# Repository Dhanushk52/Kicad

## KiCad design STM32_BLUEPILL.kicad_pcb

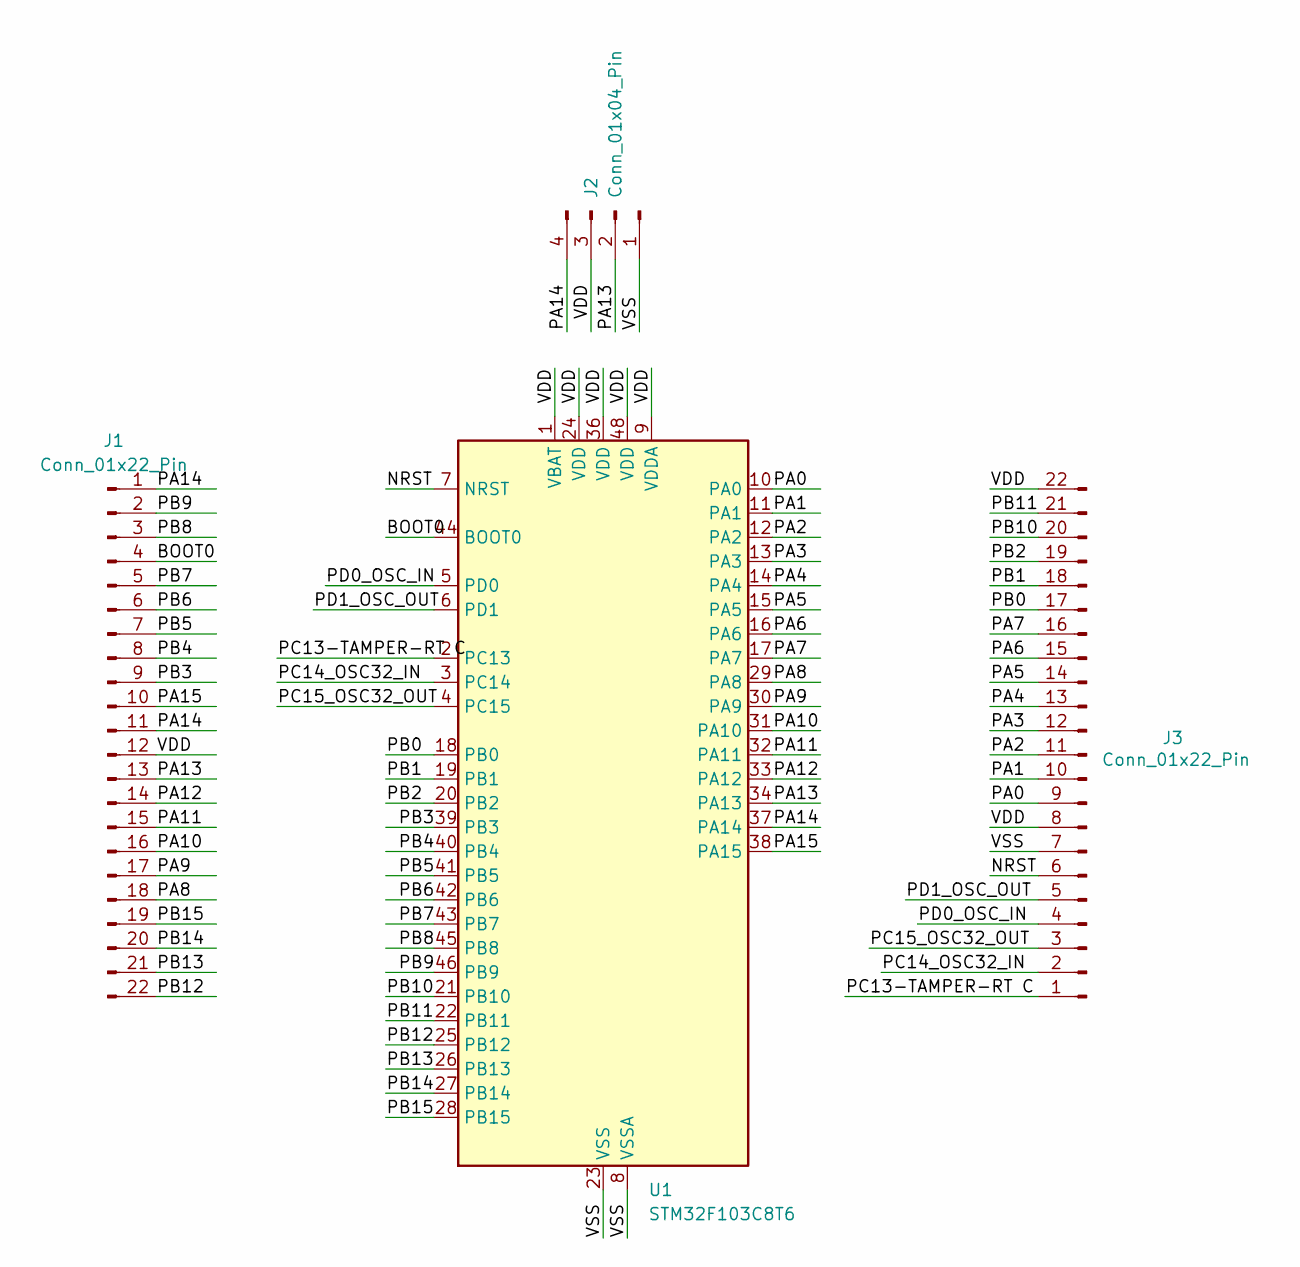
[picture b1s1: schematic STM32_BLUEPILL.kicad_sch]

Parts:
J1, J3: Conn_01x22_Pin; PinHeader_1x22_P2.54mm_Vertical
J2: Conn_01x04_Pin; PinHeader_1x04_P2.54mm_Horizontal
U1: STM32F103C8T6; LQFP-48_7x7mm_P0.5mm

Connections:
/BOOT0: J1.4, U1.44 (BOOT0)
/NRST: J3.6, U1.7 (NRST)
/PA0: J3.9, U1.10 (PA0)
/PA1: J3.10, U1.11 (PA1)
/PA2: J3.11, U1.12 (PA2)
/PA3: J3.12, U1.13 (PA3)
/PA4: J3.13, U1.14 (PA4)
/PA5: J3.14, U1.15 (PA5)
/PA6: J3.15, U1.16 (PA6)
/PA7: J3.16, U1.17 (PA7)
/PA8: J1.18, U1.29 (PA8)
/PA9: J1.17, U1.30 (PA9)
/PA10: J1.16, U1.31 (PA10)
/PA11: J1.15, U1.32 (PA11)
/PA12: J1.14, U1.33 (PA12)
/PA13: J1.13, J2.2, U1.34 (PA13)
/PA14: J1.1, J1.11, J2.4, U1.37 (PA14)
/PA15: J1.10, U1.38 (PA15)
/PB0: J3.17, U1.18 (PB0)
/PB1: J3.18, U1.19 (PB1)
/PB2: J3.19, U1.20 (PB2)
/PB3: J1.9, U1.39 (PB3)
/PB4: J1.8, U1.40 (PB4)
/PB5: J1.7, U1.41 (PB5)
/PB6: J1.6, U1.42 (PB6)
/PB7: J1.5, U1.43 (PB7)
/PB8: J1.3, U1.45 (PB8)
/PB9: J1.2, U1.46 (PB9)
/PB10: J3.20, U1.21 (PB10)
/PB11: J3.21, U1.22 (PB11)
/PB12: J1.22, U1.25 (PB12)
/PB13: J1.21, U1.26 (PB13)
/PB14: J1.20, U1.27 (PB14)
/PB15: J1.19, U1.28 (PB15)
/PC13-TAMPER-RT C: J3.1, U1.2 (PC13)
/PC14_OSC32_IN: J3.2, U1.3 (PC14)
/PC15_OSC32_OUT: J3.3, U1.4 (PC15)
/PD0_OSC_IN: J3.4, U1.5 (PD0)
/PD1_OSC_OUT: J3.5, U1.6 (PD1)
/VDD: J1.12, J2.3, J3.8, J3.22, U1.1 (VBAT), U1.9 (VDDA), U1.24 (VDD), U1.36 (VDD), U1.48 (VDD)
/VSS: J2.1, J3.7, U1.8 (VSSA), U1.23 (VSS), U1.35 (VSS), U1.47 (VSS)

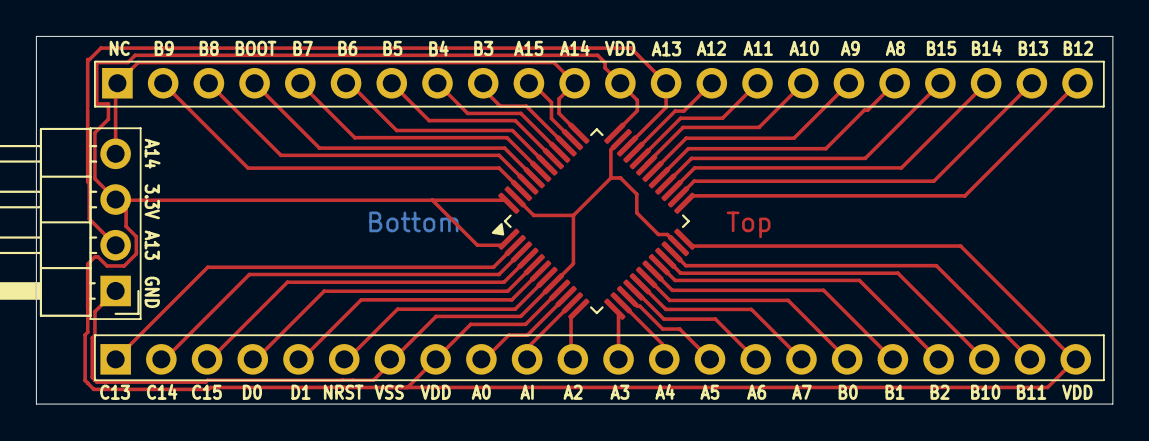
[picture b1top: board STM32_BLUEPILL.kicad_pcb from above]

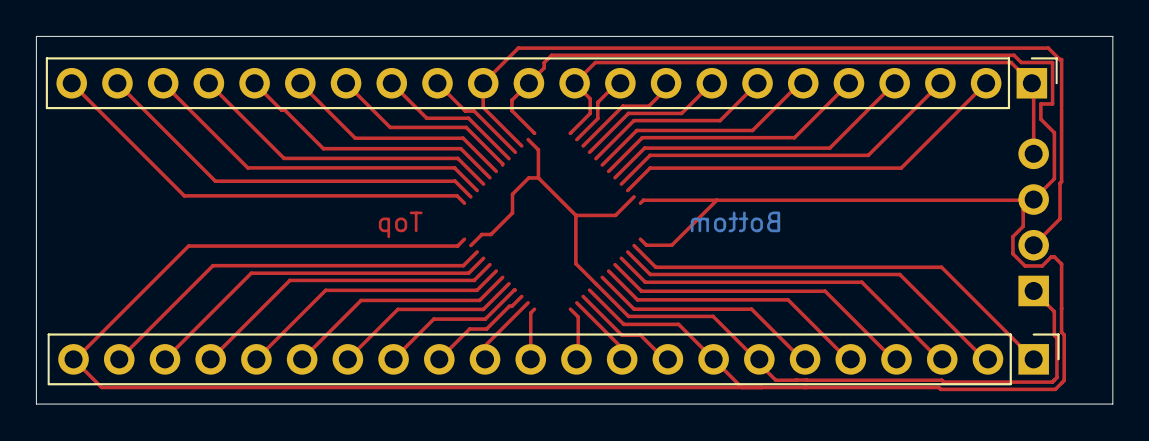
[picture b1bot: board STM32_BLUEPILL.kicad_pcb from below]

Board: 2 copper layers, 59.8 x 20.4 mm, 4 parts (2 on the bottom side), 41 nets.

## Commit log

2025-07-07 Add files via upload
    Old design
2025-07-08 Add files via upload
    Mid
2025-07-08 Add files via upload
    Updated PCB design (STM32BLUEPILL)
